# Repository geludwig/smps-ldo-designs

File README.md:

# smps-ldo-designs
This repository includes finished SMPS and LDO (SwitchModePowerSupply and LowDropoutRegulator) designs.

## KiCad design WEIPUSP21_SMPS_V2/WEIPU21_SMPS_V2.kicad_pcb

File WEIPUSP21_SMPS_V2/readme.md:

This SMPS fits into a WEIPU SP21 connector, uses 0603 component size and features a UVLO.

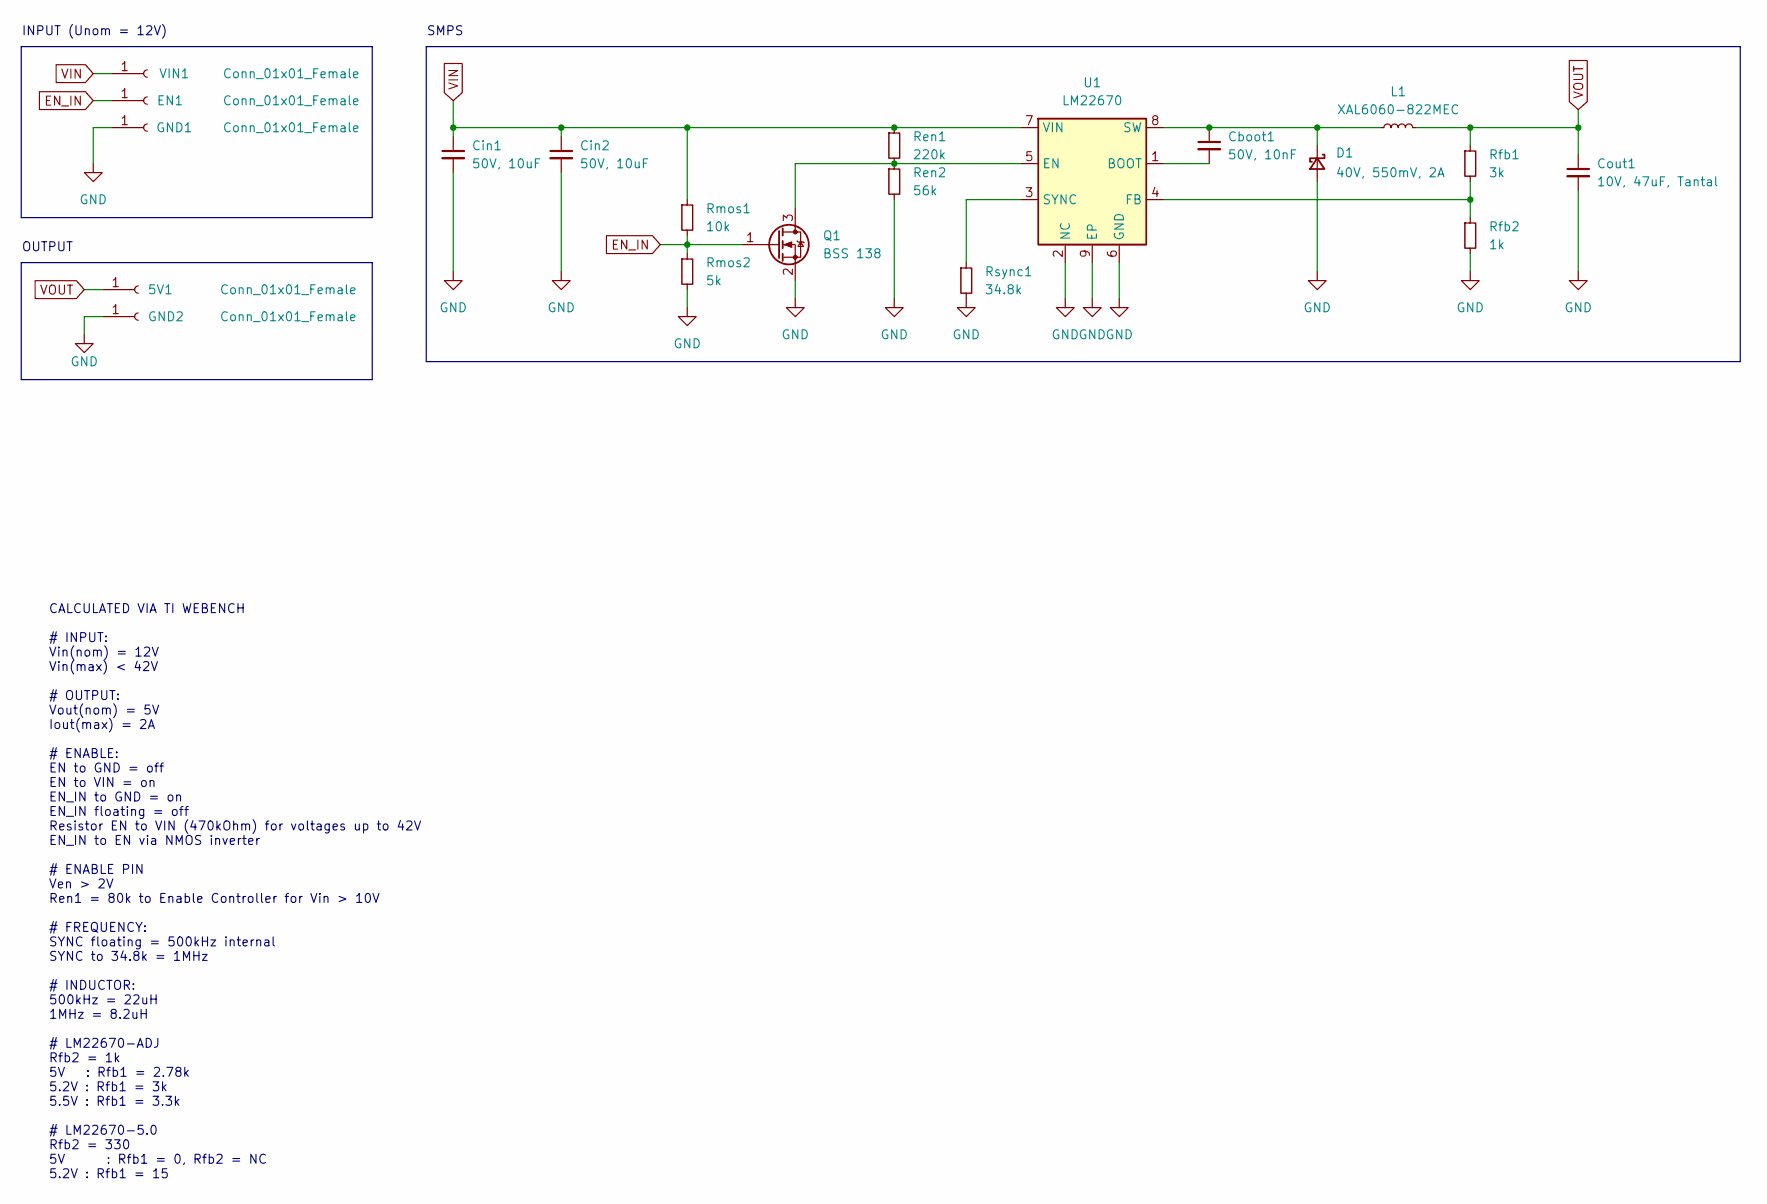
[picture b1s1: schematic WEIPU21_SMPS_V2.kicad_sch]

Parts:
5V1: Conn_01x01_Female; TestPoint_THTPad_D1.0mm_Drill0.5mm
Cboot1: 50V, 10nF; C_0603_1608Metric
Cin1, Cin2: 50V, 10uF; C_1210_3225Metric
Cout1: 10V, 47uF, Tantal; CP_EIA-3528-21_Kemet-B
D1: 40V, 550mV, 2A; D_SOD-128
EN1: Conn_01x01_Female; TestPoint_THTPad_D1.0mm_Drill0.5mm
GND1: Conn_01x01_Female; SolderWirePad_1x01_SMD_1x2mm
GND2: Conn_01x01_Female; TestPoint_THTPad_D1.0mm_Drill0.5mm
L1: XAL6060-822MEC; L_Coilcraft_XAL60xx_6.36x6.56mm
Q1: BSS 138; SOT-23W
Ren1: 220k; R_0603_1608Metric
Ren2: 56k; R_0603_1608Metric
Rfb1: 3k; R_0603_1608Metric
Rfb2: 1k; R_0603_1608Metric
Rmos1: 10k; R_0603_1608Metric
Rmos2: 5k; R_0603_1608Metric
Rsync1: 34.8k; R_0603_1608Metric
U1: LM22670; TI_SO-PowerPAD-8
VIN1: Conn_01x01_Female; SolderWirePad_1x01_SMD_1x2mm

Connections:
EN_IN: EN1.1, Q1.1 (G), Rmos1.2, Rmos2.1
GND: Cin1.2, Cin2.2, Cout1.2, D1.2 (A), GND1.1, GND2.1, Q1.2 (S), Ren2.2, Rfb2.2, Rmos2.2, Rsync1.2, U1.2 (NC), U1.6 (GND), U1.9 (EP)
unnamed: Cboot1.1, D1.1 (K), L1.1, U1.8 (SW)
unnamed: Cboot1.2, U1.1 (BOOT)
unnamed: Q1.3 (D), Ren1.2, Ren2.1, U1.5 (EN)
unnamed: Rfb1.2, Rfb2.1, U1.4 (FB)
unnamed: Rsync1.1, U1.3 (SYNC)
VIN: Cin1.1, Cin2.1, Ren1.1, Rmos1.1, U1.7 (VIN), VIN1.1
VOUT: 5V1.1, Cout1.1, L1.2, Rfb1.1

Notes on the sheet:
OUTPUT
INPUT (Unom = 12V)
SMPS
CALCULATED VIA TI WEBENCH # INPUT: Vin(nom) = 12V Vin(max) < 42V # OUTPUT: Vout(nom) = 5V Iout(max) = 2A # ENABLE: EN to GND = off EN to VIN = on EN_IN to GND = on EN_IN floating = off Resistor EN to VIN (470kOhm) for voltages up to 42V EN_IN to EN via NMOS inverter # ENABLE PIN Ven > 2V Ren1 = 80k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

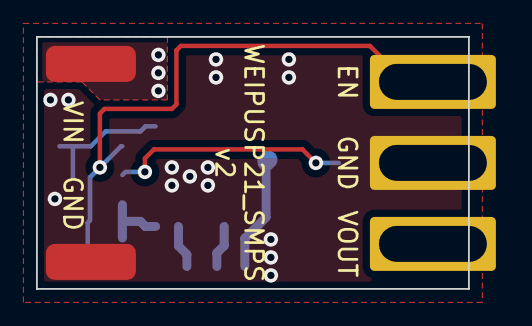
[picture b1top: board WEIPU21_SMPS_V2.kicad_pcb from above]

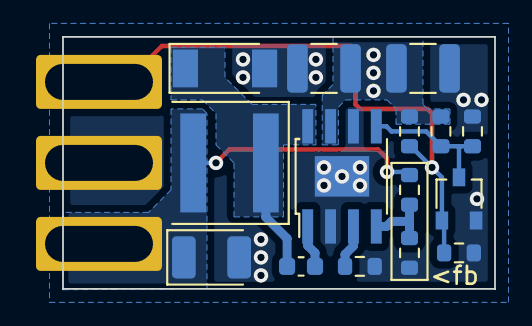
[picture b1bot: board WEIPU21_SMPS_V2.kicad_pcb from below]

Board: 2 copper layers, 24.0 x 14.0 mm, 20 parts (15 on the bottom side), 9 nets.
